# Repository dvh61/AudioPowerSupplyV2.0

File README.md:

# AudioPowerSupplyV2.0
Testing of Kicad/Github capabilities

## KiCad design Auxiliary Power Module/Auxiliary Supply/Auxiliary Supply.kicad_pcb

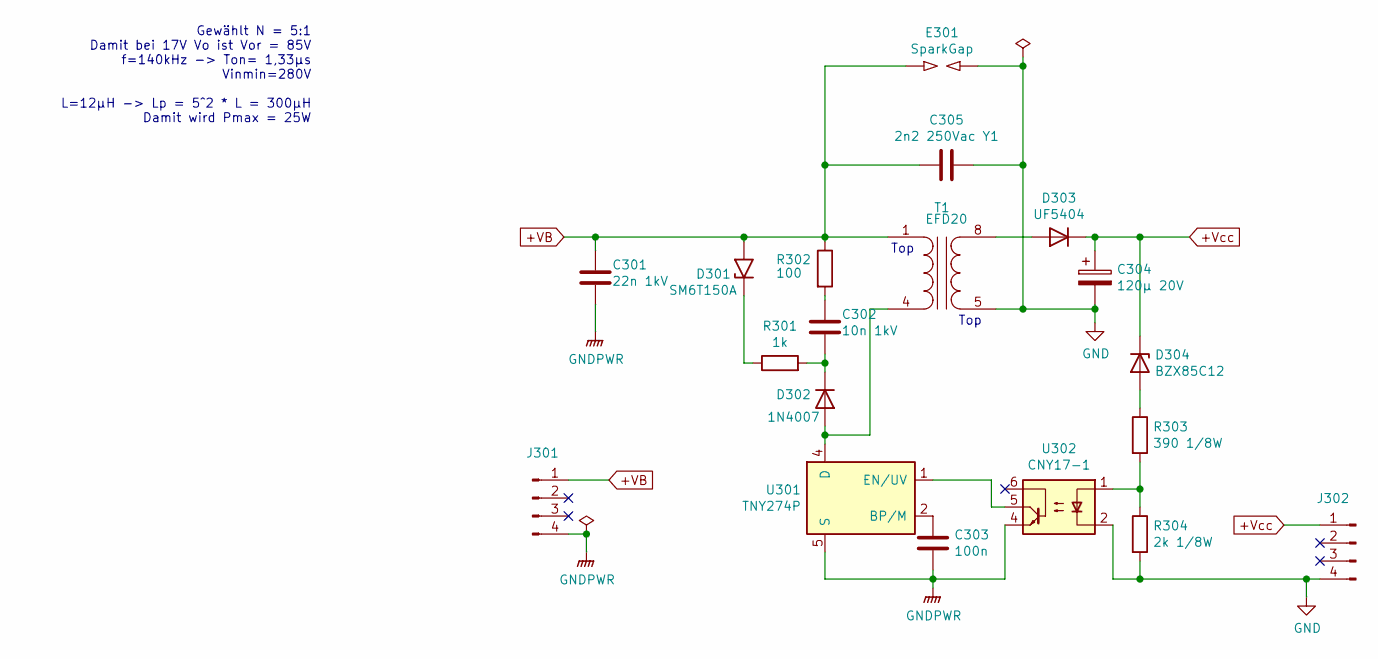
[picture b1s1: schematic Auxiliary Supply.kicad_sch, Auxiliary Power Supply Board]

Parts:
C301: 22n 1kV; C_Disc_D12.5mm_W5.0mm_P7.50mm
C302: 10n 1kV; C_Disc_D12.5mm_W5.0mm_P7.50mm
C303: 100n; C_Rect_L7.2mm_W2.5mm_P5.00mm_FKS2_FKP2_MKS2_MKP2
C304: 120µ 20V; CP_Radial_D6.3mm_P2.50mm
C305: 2n2 250Vac Y1; C_Rect_L18.0mm_W7.0mm_P15.00mm_FKS3_FKP3
D301: SM6T150A; D_SMB_Handsoldering
D302: 1N4007; D_DO-41_SOD81_P2.54mm_Vertical_KathodeUp
D303: UF5404; D_DO-41_SOD81_P2.54mm_Vertical_KathodeUp
D304: BZX85C12; D_DO-41_SOD81_P3.81mm_Vertical_KathodeUp
E301: SparkGap; SparkGap 5000V Top
J301, J302: Conn_01x04_Male; PinHeader_1x04_P2.54mm_Vertical
R301: 1k; R_Axial_DIN0309_L9.0mm_D3.2mm_P5.08mm_Vertical
R302: 100; R_Axial_DIN0309_L9.0mm_D3.2mm_P12.70mm_Horizontal
R303: 390 1/8W; R_Axial_DIN0207_L6.3mm_D2.5mm_P2.54mm_Vertical
R304: 2k 1/8W; R_Axial_DIN0207_L6.3mm_D2.5mm_P2.54mm_Vertical
T1: B66418W1008D1; Mouser Part Number 871-B66418W1008D1
U301: TNY274P; PowerIntegrations_PDIP-8C
U302: CNY17-1; DIP-6_W7.62mm_LongPads

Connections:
+VB: C301.1, C305.1, D301.2 (A2), E301.1, J301.1, R302.1, T1.1 (AA)
+Vcc: C304.1, D303.1 (K), D304.1 (K), J302.1
GND: C304.2, C305.2, E301.2, J302.4, R304.2, T1.5 (SA), U302.2
GNDPWR: C301.2, C303.2, J301.4, U301.5 (S), U301.6 (S), U301.7 (S), U301.8 (S), U302.4
unnamed: C302.1, R302.2
unnamed: C302.2, D302.1 (K), R301.2
unnamed: C303.1, U301.2 (BP/M)
unnamed: D301.1 (A1), R301.1
unnamed: D302.2 (A), T1.4 (AB), U301.4 (D)
unnamed: D303.2 (A), T1.8 (SB)
unnamed: D304.2 (A), R303.1
unnamed: R303.2, R304.1, U302.1
unnamed: U301.1 (EN/UV), U302.5

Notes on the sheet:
Gewählt N = 5:1 Damit bei 17V Vo ist Vor = 85V f=140kHz -> Ton= 1,33µs Vinmin=280V L=12µH -> Lp = 5^2 * L = 300µH Damit wird Pmax = 25W
Top

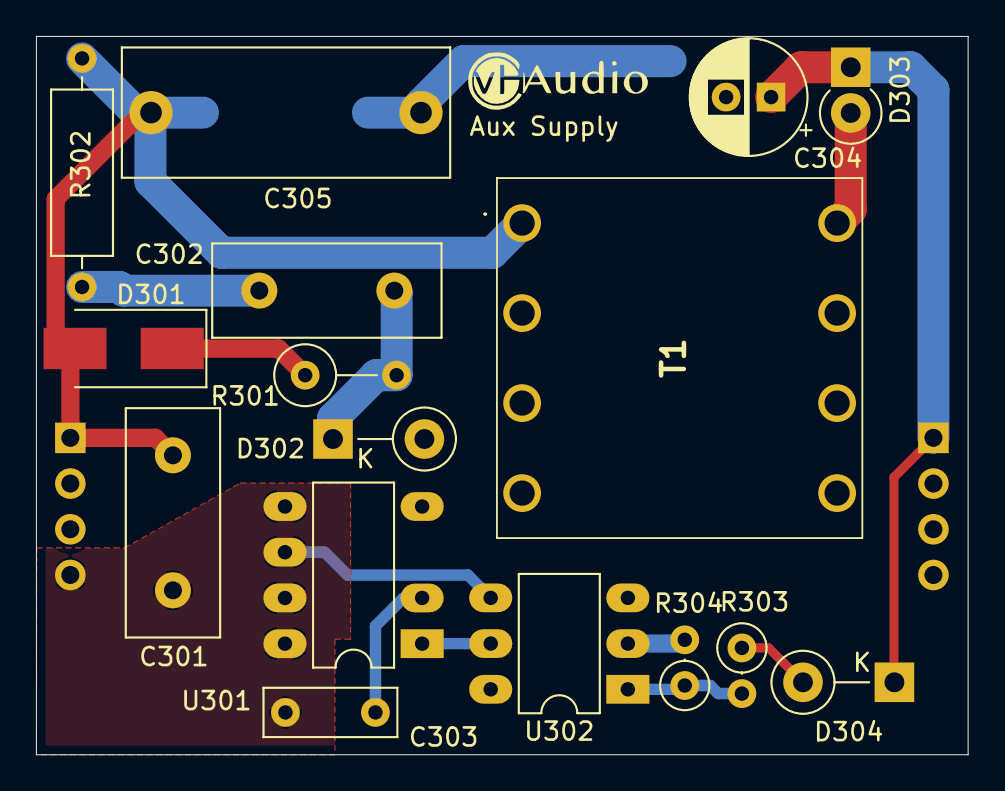
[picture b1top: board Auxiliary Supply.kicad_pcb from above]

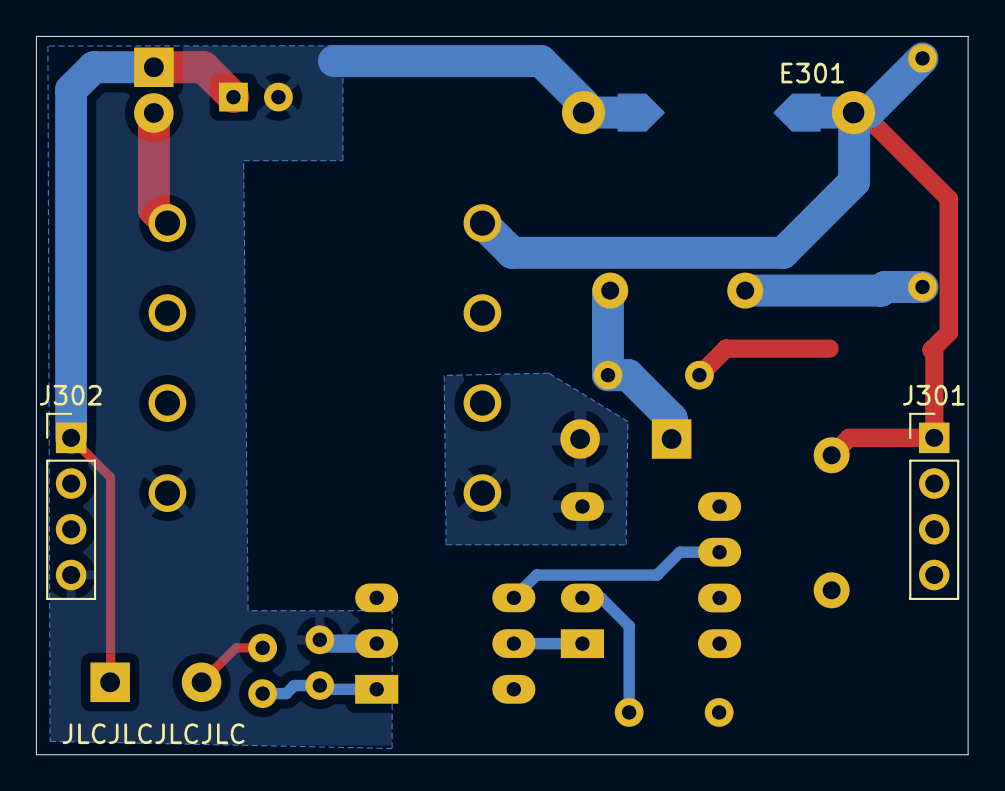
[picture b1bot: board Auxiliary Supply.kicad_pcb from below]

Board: 2 copper layers, 51.8 x 39.9 mm, 19 parts (3 on the bottom side), 13 nets.

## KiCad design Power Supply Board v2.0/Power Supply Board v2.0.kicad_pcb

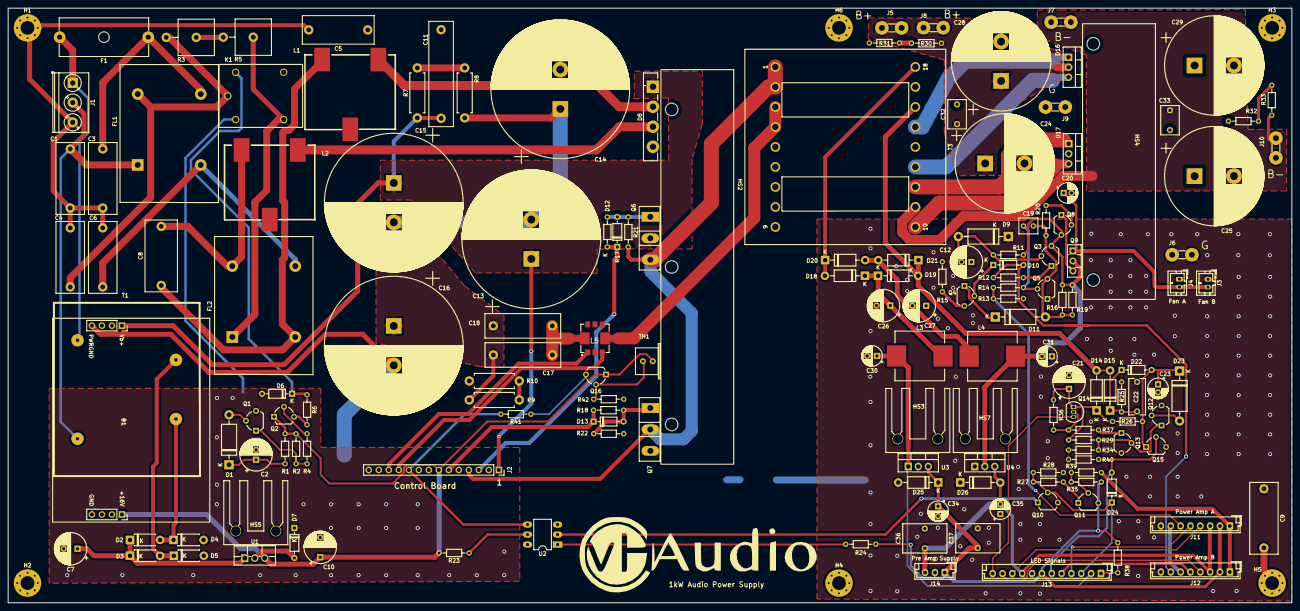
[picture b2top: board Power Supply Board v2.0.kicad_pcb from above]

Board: 2 copper layers, 326.0 x 151.0 mm, 164 parts (1 on the bottom side), 92 nets.

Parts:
B1: AuxPowerSupplyBoard; Aux Power Supply Board
C1, C3, C4, C5, C6, C9: Y2 1n2/500; C_Rect_L18.0mm_W7.0mm_P15.00mm_FKS3_FKP3
C2: 15µ/25; CP_Radial_D8.0mm_P2.50mm
C7, C21, C26, C27: 470µ/35; CP_Radial_D8.0mm_P3.50mm
C8: X2 220n/400; C_Rect_L18.0mm_W8.0mm_P15.00mm_FKS3_FKP3
C10: 47µ/25; CP_Radial_D8.0mm_P5.00mm
C11: 470n/400; C_Rect_L26.5mm_W6.0mm_P22.50mm_MKS4
C12: 1/50; CP_Radial_D8.0mm_P2.50mm
C13, C14, C15, C16: 2200µ/200V; CP_Radial_D35.0mm_P10.00mm_SnapIn
C17, C18: 27n/300V; C_Rect_L19.0mm_W6.0mm_P15.00mm_MKS4
C19: 10n; C_Rect_L4.6mm_W3.8mm_P2.50mm_MKS02_FKP02
C20: 4.7µ/50; CP_Radial_D5.0mm_P2.00mm
C22: 100n; C_Rect_L9.0mm_W4.0mm_P7.50mm_MKT
C23: 33µ/35; CP_Radial_D5.0mm_P2.00mm
C24, C25, C28, C29: 680µ/200V; CP_Radial_D25.0mm_P10.00mm_SnapIn
C30, C31: 47µ/35; CP_Radial_D5.0mm_P2.50mm
C32, C33: 100n/100; C_Rect_L7.2mm_W4.5mm_P5.00mm_FKS2_FKP2_MKS2_MKP2
C34, C35: 10µ/35; CP_Radial_D5.0mm_P2.50mm
C36, C37: 470n; C_Rect_L7.2mm_W11.0mm_P5.00mm_FKS2_FKP2_MKS2_MKP2
D1, D11: 8V2; D_DO-15_P12.70mm_Horizontal
D2, D3, D4, D5: 1N4004; D_DO-41_SOD81_P7.62mm_Horizontal
D6, D7, D10, D12, D13, D22, D24: 1N4148; D_DO-35_SOD27_P7.62mm_Horizontal
D8: GBU2506G; Diode_Bridge_Vishay_GBU
D9, D23: 15V; D_DO-15_P12.70mm_Horizontal
D14, D15, D18, D19, D20, D21: MUR120; D_DO-41_SOD81_P10.16mm_Horizontal
D16, D17: MUR1620CTG; TO-220-3_Vertical
D25, D26: 1N4001; D_DO-41_SOD81_P10.16mm_Horizontal
E1: SparkGap; SparkGap 5000V Top
F1: T6A; Fuseholder_Cylinder-5x20mm_Schurter_0031_8201_Horizontal_Op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
FL1: 7mH/7A; L_CommonMode_Toroid_Vertical_L35mm_W25mm_Px19mm_Py18mm_Keme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
FL2: 7mH//A; L_CommonMode_Toroid_Vertical_L35mm_W25mm_Px19mm_Py18mm_Keme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
H1, H5: MountingHole_Pad; MountingHole_3.5mm_Pad_Via
H2, H3, H4, H6: MountingHole; MountingHole_3.5mm_Pad_Via
HS2: Heatsink; Heatsink_100x45x18mm_3xFixationM3
HS3, HS5, HS7: Heatsink; Heatsink EA2 T220
HS4: Heatsink; Heatsink_70x45x18mm_2xFixationM3
J1: CONN_01X03; TerminalBlock_Phoenix_PT-1,5-3-5.0-H_1x03_P5.00mm_Horizontal
J2: CON_CTRL_Board; PinSocket_1x14_P2.54mm_Vertical
J3, J4: CONN_01X02; JST_PH_B2B-PH-K_1x02_P2.00mm_Vertical
J5, J8: +BH; PCB_Connector_6.35x0.81mm_Vertical
J6, J9: G; PCB_Connector_6.35x0.81mm_Vertical
J7, J10: -BH; PCB_Connector_6.35x0.81mm_Vertical
J11: CON_AMP_A; JST_EH_B8B-EH-A_1x08_P2.50mm_Vertical
J12: CON_AMP_B; JST_EH_B8B-EH-A_1x08_P2.50mm_Vertical
J13: CON_LED; JST_EH_B12B-EH-A_1x12_P2.50mm_Vertical
J14: CONN_01X03; JST_EH_B3B-EH-A_1x03_P2.50mm_Vertical
K1: Pana JS1-12V-F; FINDER_36.11
L1, L2: 57µ/10Arms; L_muRata_6000A
L3, L4: 10µ; L_Wuerth_WE-PD-Typ-LS_Handsoldering
L5: 53100C-I-XFR; 53100C
Q1, Q10, Q11, Q12, Q13, Q15: BC546; TO-92_Wide
Q2, Q4, Q16: MPSA06; TO-92_Wide
Q3, Q5, Q8: MPSA56; TO-92_Wide
Q6, Q7: IRFP460; TO-247-3_Vertical
Q9: MJE350; TO-126-3_Vertical
Q14: MPSA56; TO-92_Inline
R1: 68k; R_Axial_DIN0204_L3.6mm_D1.6mm_P7.62mm_Horizontal
R2: 470; R_Axial_DIN0204_L3.6mm_D1.6mm_P7.62mm_Horizontal
R3, R5: 15/5W; R_Axial_Power_L25.0mm_W9.0mm_P7.62mm_Vertical
R4, R21, R22, R28, R35: 1k; R_Axial_DIN0204_L3.6mm_D1.6mm_P7.62mm_Horizontal
R6: 120; R_Axial_DIN0204_L3.6mm_D1.6mm_P7.62mm_Horizontal
R7, R8, R9, R10: 47k/0.5W; R_Axial_DIN0411_L9.9mm_D3.6mm_P12.70mm_Horizontal
R11: 8k2; R_Axial_DIN0204_L3.6mm_D1.6mm_P7.62mm_Horizontal
R12: 5k6; R_Axial_DIN0204_L3.6mm_D1.6mm_P7.62mm_Horizontal
R13, R14: 330; R_Axial_DIN0204_L3.6mm_D1.6mm_P7.62mm_Horizontal
R15, R20: 220; R_Axial_DIN0204_L3.6mm_D1.6mm_P7.62mm_Horizontal
R16, R23, R41: 12k; R_Axial_DIN0204_L3.6mm_D1.6mm_P7.62mm_Horizontal
R17, R18: 10; R_Axial_DIN0204_L3.6mm_D1.6mm_P7.62mm_Horizontal
R19: 18k; R_Axial_DIN0204_L3.6mm_D1.6mm_P7.62mm_Horizontal
R24: 680; R_Axial_DIN0204_L3.6mm_D1.6mm_P7.62mm_Horizontal
R25: 4k7; R_Axial_DIN0204_L3.6mm_D1.6mm_P7.62mm_Horizontal
R26: 150k; R_Axial_DIN0204_L3.6mm_D1.6mm_P7.62mm_Horizontal
R27, R38, R39: 10k; R_Axial_DIN0204_L3.6mm_D1.6mm_P7.62mm_Horizontal
R29, R36, R37: 220k; R_Axial_DIN0204_L3.6mm_D1.6mm_P7.62mm_Horizontal
R30, R31, R32, R33, R34: 100k; R_Axial_DIN0204_L3.6mm_D1.6mm_P7.62mm_Horizontal
R40: 56k; R_Axial_DIN0204_L3.6mm_D1.6mm_P7.62mm_Horizontal
R42: 120k; R_Axial_DIN0204_L3.6mm_D1.6mm_P7.62mm_Horizontal
T1: Transformer_1P_1S; Transformer_Block_EI42_VC-05VA_1xSec
T3: Half_Bridge_Transformer; ETD44_18Pin_Horizontal_EPCOS-B663661018T
TH1: Thermistor_PTC; PTC Epcos D1052
U1: LM7815ACT; TO-220F-3_Vertical
U2: CNY75G; DIP-6_W7.62mm_LongPads
U3: LM7815ACT; TO-220-3_Vertical
U4: LM7915CT; TO-220-3_Vertical

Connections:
+15V: C34.1, C37.1, D25.1 (K), J11.2, J12.2, J13.7, J14.1, Q11.3 (E), R24.2, R35.2, R38.2, U3.3 (VO)
+16V: B1.5 (+16V), C10.1, J2.7, Q2.1 (E), Q16.1 (E), R1.2, R2.2, R23.2, TH1.1, U1.3 (VO)
+24V: C30.1, J13.2, L3.1, U3.1 (VI)
-15V: C35.2, C36.1, D26.2 (A), J11.3, J12.3, J13.9, J14.3, U4.3 (VO)
-24V: C31.2, L4.1, Q3.3 (C), Q8.3 (C), Q9.2 (C), R11.1, R16.1, R19.1, U4.2 (VI)
/L: F1.2, J1.1, T1.1 (AA)
/N: C1.1, FL1.1, J1.2, T1.2 (AB)
/PR1: J11.6, R13.1, R14.2
/PR2: D10.2 (A), J12.7, R12.2
CLIP_A: J11.5, J13.4
CLIP_B: J12.5, J13.5
CS+: J2.11, L5.3 (SEC2)
CS-: J2.12, L5.1 (SEC1)
Earth_Protective: C1.2, C3.2, C4.2, C5.2, C6.2, H1.1, J1.3
FAULT: D24.1 (K), J13.3, Q10.2 (B), R27.1, R28.2
GND: C9.1, C12.1, C20.2, C21.2, C22.2, C23.2, C24.2, C25.1, C26.2, C27.1, C28.2, C29.1, C30.2, C31.1, C32.2, C33.1, C34.2, C35.1, C36.2, C37.2, D9.1 (K), D17.2 (common), D25.2 (A), D26.1 (K), E1.2, J3.1, J4.1, J6.1, J9.1, J11.8, J12.8, J13.8, J14.2, Q5.1 (E), Q10.3 (E), Q12.3 (E), Q13.3 (E), Q15.3 (E), R13.2, R15.2, R25.2, R28.1, R31.2, R32.1, R34.2, R40.2, T3.14, T3.17, U3.2 (GND), U4.1 (GND)
GNDA: B1.4 (PWRGND), B1.8 (GND), C2.2, C5.1, C7.2, C10.2, C11.1, C14.2, C16.2, D4.2 (A), D5.2 (A), D6.2 (A), D7.1 (K), D8.4 (-), E1.1, J2.14, K1.A1, Q1.3 (E), Q7.3 (S), R10.2, R22.2, R42.2
HO: D12.1 (K), J2.3, R17.2
LO: D13.1 (K), J2.6, R18.2
MUTE: J13.12, Q14.3 (C)
unnamed: C2.1, D1.1 (K), R1.1
unnamed: C3.1, F1.1, FL1.3
unnamed: C4.1, FL1.4, K1.11, R3.2
unnamed: C6.1, FL1.2, FL2.3
unnamed: C7.1, D2.1 (K), D3.1 (K), U1.1 (VI)
unnamed: C8.1, FL2.2, L1.2
unnamed: C8.2, FL2.4, L2.2
unnamed: C9.2, H5.1
unnamed: C12.2, D9.2 (A), Q3.2 (B), R11.2
unnamed: C13.2, C14.1, C15.2, C16.1, C17.2, C18.1, R8.2, R9.1
unnamed: C17.1, C18.2, L5.8 (PRI2)
unnamed: C19.1, Q5.2 (B), R14.1
unnamed: C19.2, D11.2 (A), Q5.3 (C), R16.2, R19.2, R20.2
unnamed: C20.1, J3.2, J4.2, Q9.1 (E)
unnamed: C21.1, D14.1 (K), Q14.1 (E), R26.1, R29.1, R36.1
unnamed: C22.1, D15.1 (K), D22.1 (K), R25.1
unnamed: C23.1, D22.2 (A), D23.1 (K), Q15.1 (C), R26.2
unnamed: C24.1, C28.1, C32.1, D16.2 (common), J5.1, J8.1, R30.1
unnamed: C25.2, C29.2, C33.2, J7.1, J10.1, R33.2, T3.11
unnamed: C26.1, D18.1 (K), D19.1 (K), L3.2
unnamed: C27.2, D20.2 (A), D21.2 (A), L4.2
unnamed: D1.2 (A), Q1.2 (B)
unnamed: D2.2 (A), D4.1 (K), T1.4 (SB)
unnamed: D3.2 (A), D5.1 (K), T1.3 (SA)
unnamed: D6.1 (K), K1.A2, R6.1
unnamed: D7.2 (A), U1.2 (GND)
unnamed: D8.2 (~~), L1.1
unnamed: D8.3 (~~), L2.1
unnamed: D10.1 (K), Q4.2 (B)
unnamed: D11.1 (K), Q4.1 (E)
unnamed: D12.2 (A), Q6.1 (G), R17.1, R21.1
unnamed: D13.2 (A), Q7.1 (G), R18.1, R22.1
unnamed: D14.2 (A), D15.2 (A), D19.2 (A), D21.1 (K), T3.16
unnamed: D16.1 (A1), T3.15
unnamed: D16.3 (A2), T3.13
unnamed: D18.2 (A), D20.1 (K), T3.18
unnamed: D23.2 (A), Q12.2 (B)
unnamed: FL2.1, K1.14, R5.1
unnamed: J11.1, J12.1, R39.1
unnamed: J11.7, J12.6
unnamed: L5.7 (PRI1), T3.3, T3.4
unnamed: Q1.1 (C), R2.1, R4.2
unnamed: Q2.2 (B), R4.1
unnamed: Q2.3 (C), R6.2
unnamed: Q3.1 (E), R12.1
unnamed: Q4.3 (C), R15.1
unnamed: Q8.1 (E), Q9.3 (B)
unnamed: Q8.2 (B), R20.1
unnamed: Q10.1 (C), U2.2
unnamed: Q11.1 (C), R27.2
unnamed: Q11.2 (B), R35.1, R39.2
unnamed: Q12.1 (C), Q13.2 (B), R29.2, R34.1
unnamed: Q13.1 (C), R37.2
unnamed: Q14.2 (B), R36.2, R37.1
unnamed: Q16.2 (B), R42.1, TH1.2
unnamed: Q16.3 (C), R41.1
unnamed: R3.1, R5.2
unnamed: R7.2, R8.1
unnamed: R9.2, R10.1
unnamed: R23.1, U2.5
unnamed: R24.1, U2.1
unnamed: R30.2, R31.1
unnamed: R32.2, R33.1
unnamed: D17.3 (A2), T3.10
unnamed: D17.1 (A1), T3.12
PWR: J13.1, R38.1
SIG_A: J11.4, J13.10
SIG_B: J12.4, J13.11
Shutdown: J2.10, R41.2, U2.4
TEMP: D24.2 (A), J13.6, Q15.2 (B), R40.1
VB: B1.1 (+Vb), C11.2, C13.1, C15.1, D8.1 (+), J2.1, Q6.2 (D), R7.1
VS: J2.4, Q6.3 (S), Q7.2 (D), R21.2, T3.1, T3.2

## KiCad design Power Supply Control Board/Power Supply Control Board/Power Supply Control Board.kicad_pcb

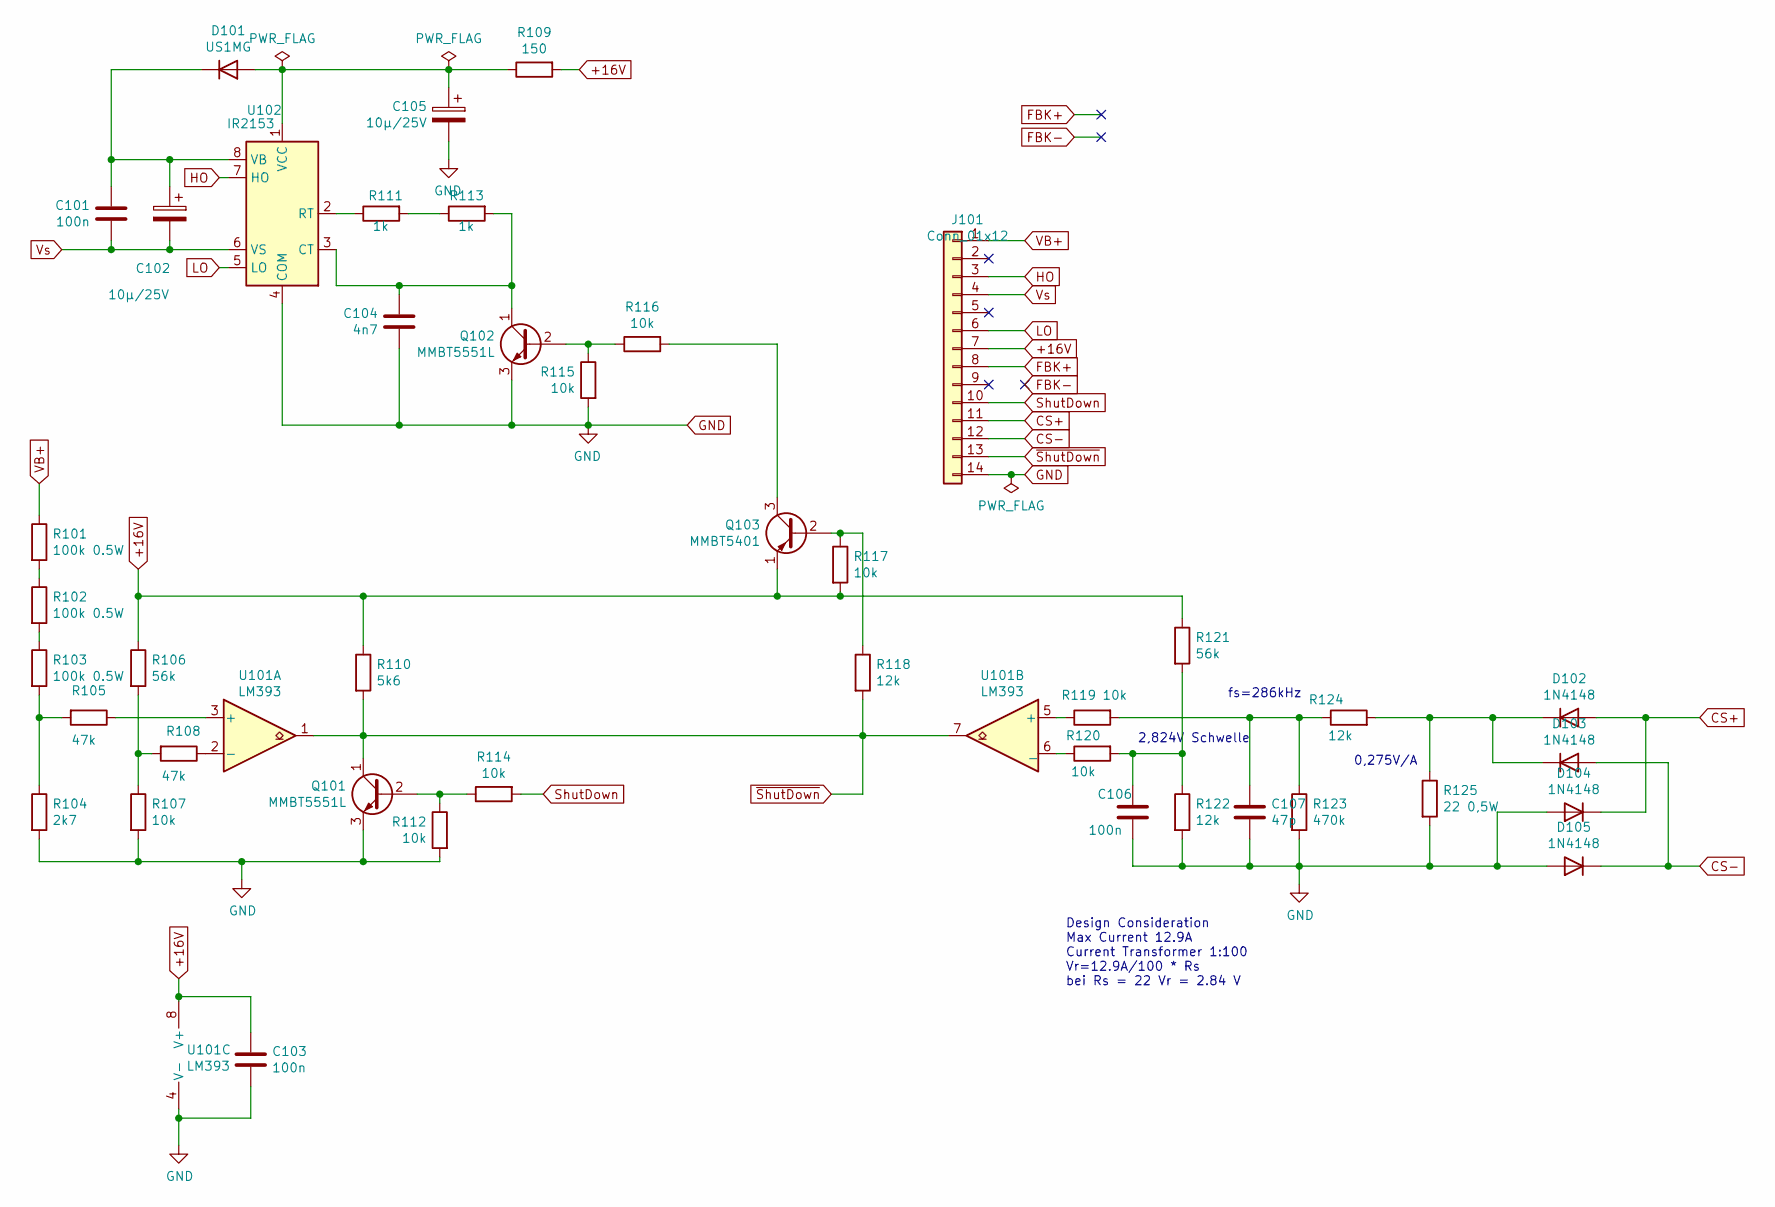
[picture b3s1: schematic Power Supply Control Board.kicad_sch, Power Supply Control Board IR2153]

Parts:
C101, C103, C106: 100n; C_0805_2012Metric
C102, C105: 10µ/25V; C_0805_2012Metric
C104: 4n7; C_0805_2012Metric
C107: 47p; C_0402_1005Metric
D101: US1MG; D_SMA
D102, D103, D104, D105: 1N4148; D_SOD-123
J101: Conn_01x12; PinHeader_1x14_P2.54mm_Horizontal
Q101, Q102: MMBT5551L; SOT-23
Q103: MMBT5401; SOT-23
R101, R102, R103: 100k 0.5W; R_1206_3216Metric
R104: 2k7; R_0805_2012Metric
R105, R108: 47k; R_0805_2012Metric
R106, R121: 56k; R_0805_2012Metric
R107, R112, R114, R115, R116, R117, R119, R120: 10k; R_0805_2012Metric
R109: 150; R_0805_2012Metric
R110: 5k6; R_0805_2012Metric
R111, R113: 1k; R_0805_2012Metric
R118, R122, R124: 12k; R_0805_2012Metric
R123: 470k; R_0805_2012Metric
R125: 22 0,5W; R_1206_3216Metric
U101: LM393; SOIC-8_3.9x4.9mm_P1.27mm
U102: IR2153; SOIC-8_3.9x4.9mm_P1.27mm; LCSC C79666

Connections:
+16V: C103.1, J101.7, Q103.1 (E), R106.1, R109.2, R110.1, R117.2, R121.1, U101.8 (V+)
CS+: D102.2 (A), D104.1 (K), J101.11
CS-: D103.2 (A), D105.1 (K), J101.12
FBK+: J101.8
GND: C103.2, C104.2, C105.2, C106.2, C107.2, D104.2 (A), D105.2 (A), J101.14, Q101.3 (E), Q102.3 (E), R104.2, R107.2, R112.2, R115.2, R122.2, R123.2, R125.2, U101.4 (V-), U102.4 (COM)
HO: J101.3, U102.7 (HO)
LO: J101.6, U102.5 (LO)
unnamed: C101.1, C102.1, D101.1 (K), U102.8 (VB)
unnamed: C104.1, Q102.1 (C), R113.2, U102.3 (CT)
unnamed: C106.1, R120.2, R121.2, R122.1
unnamed: C107.1, R119.2, R123.1, R124.1
unnamed: C105.1, D101.2 (A), R109.1, U102.1 (VCC)
unnamed: D102.1 (K), D103.1 (K), R124.2, R125.1
unnamed: Q101.2 (B), R112.1, R114.1
unnamed: Q102.2 (B), R115.1, R116.1
unnamed: Q103.2 (B), R117.1, R118.1
unnamed: Q103.3 (C), R116.2
unnamed: R101.2, R102.1
unnamed: R102.2, R103.1
unnamed: R103.2, R104.1, R105.2
unnamed: R105.1, U101.3 (+)
unnamed: R106.2, R107.1, R108.2
unnamed: R108.1, U101.2 (-)
unnamed: R111.1, U102.2 (RT)
unnamed: R111.2, R113.1
unnamed: R119.1, U101.5 (+)
unnamed: R120.1, U101.6 (_)
ShutDown: J101.10, R114.2
VB+: J101.1, R101.1
Vs: C101.2, C102.2, J101.4, U102.6 (VS)
~ShutDown: J101.13, Q101.1 (C), R110.2, R118.2, U101.1, U101.7

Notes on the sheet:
Design Consideration Max Current 12.9A Current Transformer 1:100 Vr=12.9A/100 * Rs bei Rs = 22 Vr = 2.84 V
2,824V Schwelle
fs=286kHz
0,275V/A

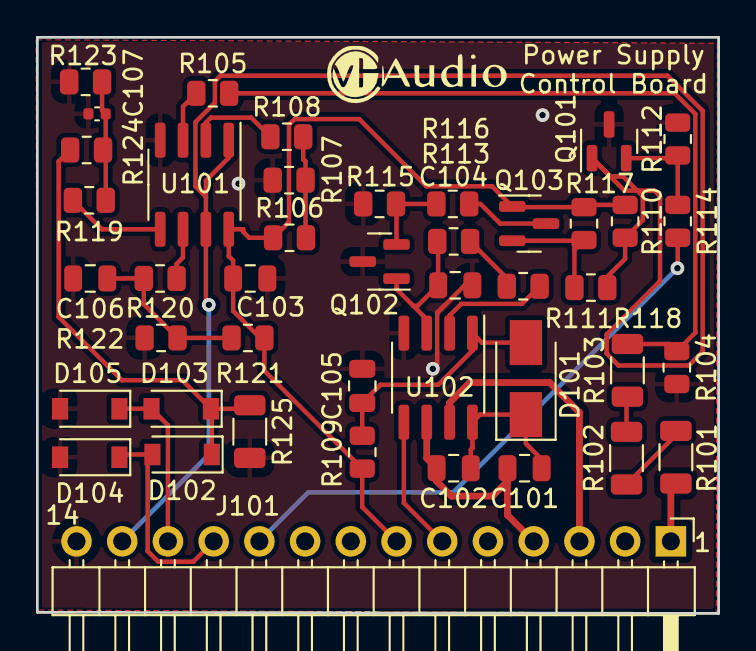
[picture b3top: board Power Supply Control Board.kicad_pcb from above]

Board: 2 copper layers, 37.8 x 32.0 mm, 43 parts (0 on the bottom side), 30 nets.

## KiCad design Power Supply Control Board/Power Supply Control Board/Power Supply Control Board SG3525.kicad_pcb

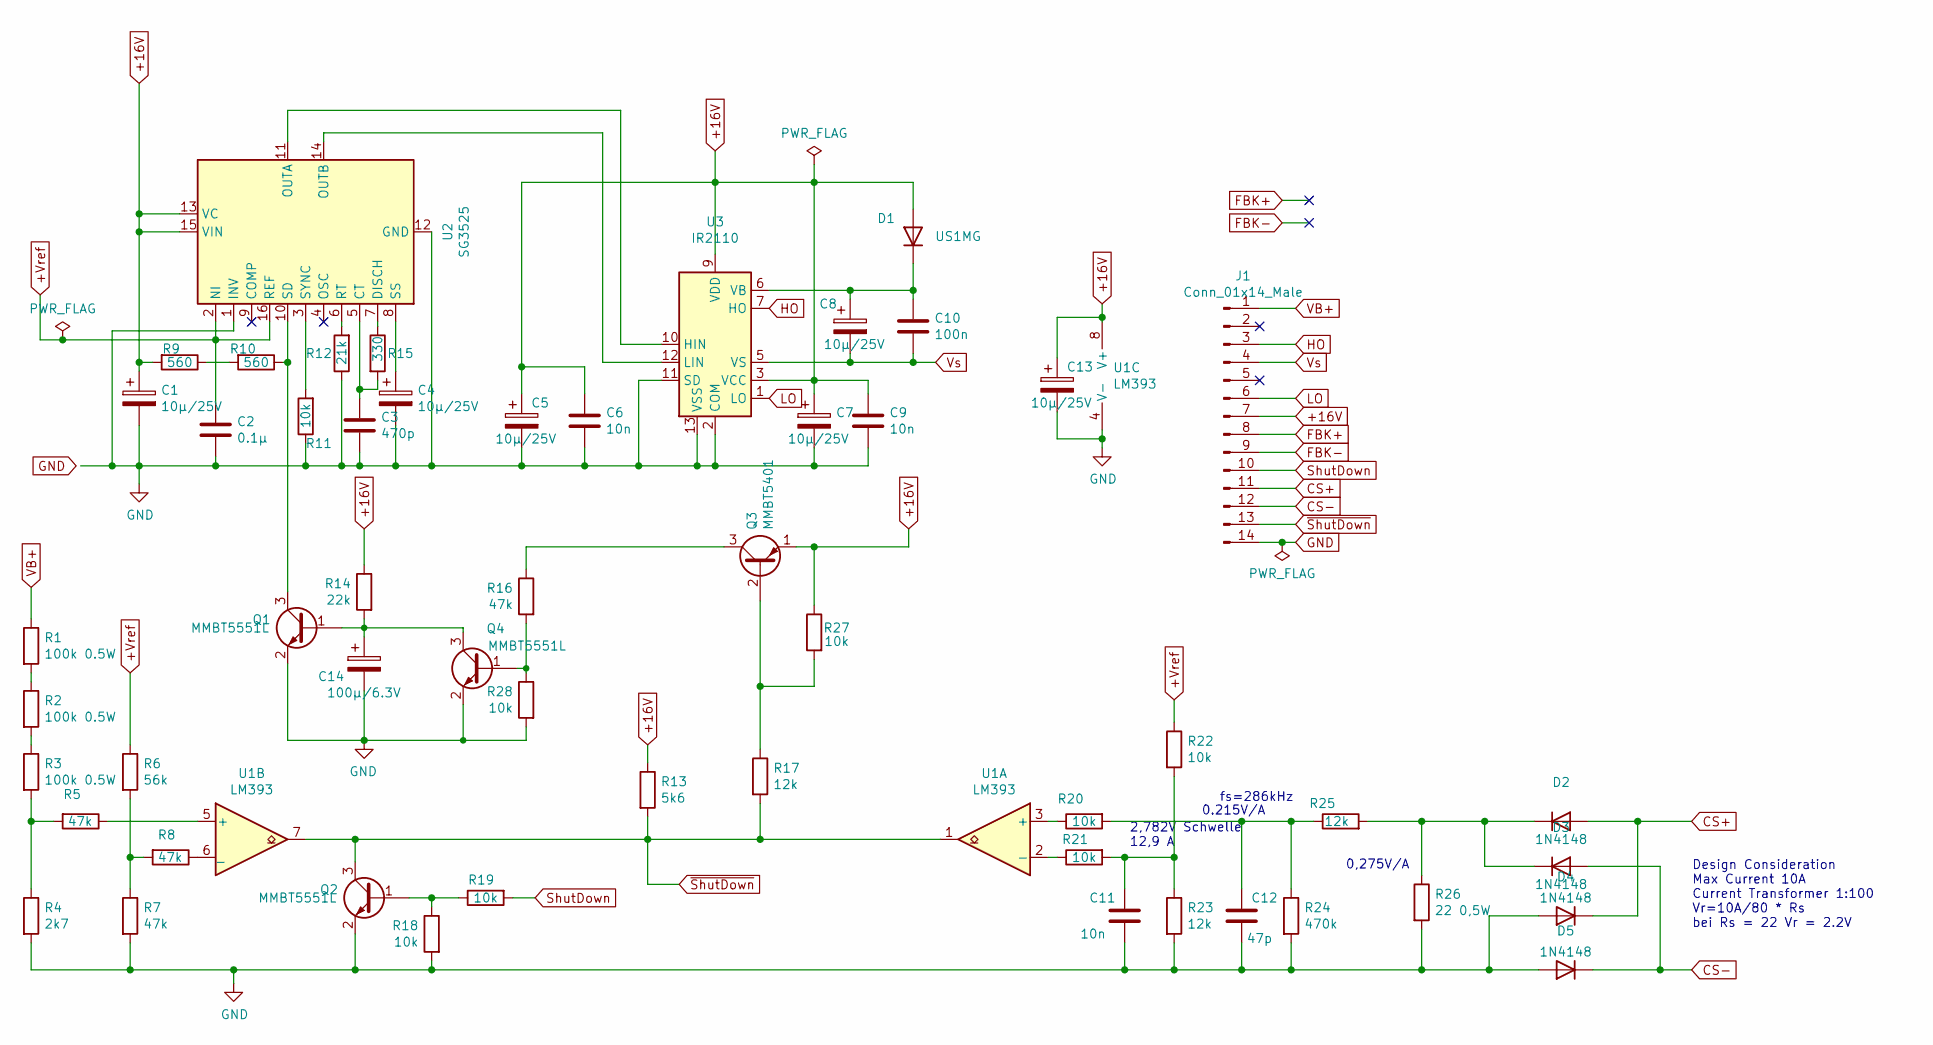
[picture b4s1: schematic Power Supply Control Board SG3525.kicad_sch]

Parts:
C1, C4, C5, C7, C8, C13: 10µ/25V; C_0805_2012Metric; LCSC C15850
C2: 0.1µ; C_0805_2012Metric; LCSC C49678
C3: 470p; C_0402_1005Metric; LCSC C1537
C6: 10n; C_0402_1005Metric; LCSC C15195
C9, C11: 10n; C_0402_1005Metric
C10: 100n; C_0805_2012Metric; LCSC C49678
C12: 47p; C_0402_1005Metric; LCSC C1567
C14: 100µ/6.3V; CP_EIA-3528-21_Kemet-B; LCSC C134723
D1: US1MG; D_SMA; LCSC C412437
D2, D3, D4, D5: 1N4148; D_SOD-123; LCSC C81598
J1: Conn_01x14_Male; PinHeader_1x14_P2.54mm_Horizontal
Q1, Q2, Q4: MMBT5551L; SOT-23
Q3: MMBT5401; SOT-23
R1, R2, R3: 100k 0.5W; R_1206_3216Metric
R4: 2k7; R_0805_2012Metric
R5, R7, R8, R16: 47k; R_0805_2012Metric
R6: 56k; R_0805_2012Metric
R9, R10: 560; R_0805_2012Metric
R11, R18, R19, R20, R21, R22, R27, R28: 10k; R_0805_2012Metric
R12: 21k; R_0805_2012Metric
R13: 5k6; R_0805_2012Metric
R14: 22k; R_0805_2012Metric
R15: 330; R_0805_2012Metric
R17, R23, R25: 12k; R_0805_2012Metric
R24: 470k; R_0805_2012Metric
R26: 22 0,5W; R_1206_3216Metric
U1: LM393; SOIC-8_3.9x4.9mm_P1.27mm
U2: SG3525; SO-16_3.9x9.9mm_P1.27mm; LCSC C68323
U3: IR2110; SOIC-16W_7.5x10.3mm_P1.27mm; LCSC C2968

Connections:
+16V: C1.1, C5.1, C6.1, C7.1, C9.1, C13.1, D1.2 (A), J1.7, Q3.1 (E), R9.2, R13.1, R14.1, R27.1, U1.8 (V+), U2.13 (VC), U2.15 (VIN), U3.3 (VCC), U3.9 (VDD)
+Vref: C2.1, R6.1, R22.1, U2.2 (NI), U2.16 (REF)
CS+: D2.2 (A), D4.1 (K), J1.11
CS-: D3.2 (A), D5.1 (K), J1.12
FBK+: J1.8
FBK-: J1.9
GND: C1.2, C2.2, C3.2, C4.2, C5.2, C6.2, C7.2, C9.2, C11.2, C12.2, C13.2, C14.2, D4.2 (A), D5.2 (A), J1.14, Q1.2 (E), Q2.2 (E), Q4.2 (E), R4.2, R7.2, R11.1, R12.1, R18.2, R23.2, R24.2, R26.2, R28.2, U1.4 (V-), U2.1 (INV), U2.12 (GND), U3.2 (COM), U3.11 (SD), U3.13 (VSS)
HO: J1.3, U3.7 (HO)
LO: J1.6, U3.1 (LO)
unnamed: C3.1, R15.2, U2.5 (CT)
unnamed: C4.1, U2.8 (SS)
unnamed: C8.1, C10.1, D1.1 (K), U3.6 (VB)
unnamed: C11.1, R21.2, R22.2, R23.1
unnamed: C12.1, R20.2, R24.1, R25.1
unnamed: C14.1, Q1.1 (B), Q4.3 (C), R14.2
unnamed: D2.1 (K), D3.1 (K), R25.2, R26.1
unnamed: Q1.3 (C), R10.1, U2.10 (SD)
unnamed: Q2.1 (B), R18.1, R19.1
unnamed: Q3.2 (B), R17.1, R27.2
unnamed: Q3.3 (C), R16.1
unnamed: Q4.1 (B), R16.2, R28.1
unnamed: R1.2, R2.1
unnamed: R2.2, R3.1
unnamed: R3.2, R4.1, R5.2
unnamed: R5.1, U1.5 (+)
unnamed: R6.2, R7.1, R8.2
unnamed: R8.1, U1.6 (_)
unnamed: R9.1, R10.2
unnamed: R11.2, U2.3 (SYNC)
unnamed: R12.2, U2.6 (RT)
unnamed: R15.1, U2.7 (DISCH)
unnamed: R20.1, U1.3 (+)
unnamed: R21.1, U1.2 (-)
unnamed: U2.11 (OUTA), U3.10 (HIN)
unnamed: U2.14 (OUTB), U3.12 (LIN)
ShutDown: J1.10, R19.2
VB+: J1.1, R1.1
Vs: C8.2, C10.2, J1.4, U3.5 (VS)
~ShutDown: J1.13, Q2.3 (C), R13.2, R17.2, U1.1, U1.7

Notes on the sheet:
2,782V Schwelle 12,9 A
0.215V/A
fs=286kHz
0,275V/A
Design Consideration Max Current 10A Current Transformer 1:100 Vr=10A/80 * Rs bei Rs = 22 Vr = 2.2V

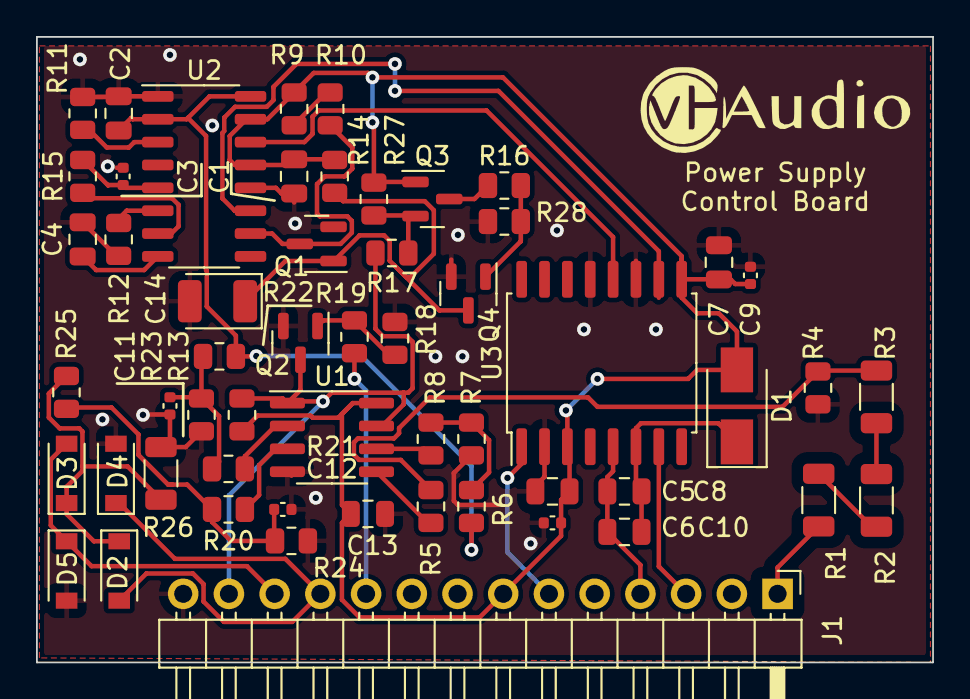
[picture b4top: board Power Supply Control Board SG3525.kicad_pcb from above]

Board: 2 copper layers, 49.8 x 34.8 mm, 55 parts (0 on the bottom side), 37 nets.

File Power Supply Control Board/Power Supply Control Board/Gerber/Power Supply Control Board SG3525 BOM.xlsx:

Comment | Designator | Footprint | LCSC Part Number
10uF | C1,C4,C5,C7,C8,C13 | 0805 | C15850
100n | C10 | 0805 | C49678
47p | C12 | 0402 | C1567
100uF | C14 | CASE-B_3528 | C16133
0.1uF | C2 | 0805 | C49678
470p | C3 | 0402 | C1537
10n | C6,C9,C11 | 0402 | C15195
US1MG | D1 | SMA | C412437
1N4148 | D2,D3,D4,D5 | SOD-123 | C81598
MMBT5551L | Q1,Q2,Q4 | SOT-23 | C2145
MMBT5401 | Q3 | SOT-23 | C8326
100k | R1,R2,R3 | 1206 | C17900
10k | R11,R18,R19,R20,R21,R22,R27,R28 | 0805 | C17414
22k | R12 | 0805 | C17560
5k6 | R13 | 0805 | C4382
22k | R14 | 0805 | C17560
330 | R15 | 0805 | C17630
470k | R24 | 0805 | C17709
22 | R26 | 1206 | C17958
2k7 | R4 | 0805 | C17530
12k | R17,R23,R25 | 0805 | C17444
47k | R5,R7,R8,R16 | 0805 | C17713
56k | R6 | 0805 | C17756
560 | R9,R10 | 0805 | C28636
LM393 | U1 | SOIC-8_3.9x4.9x1.27P | C7955
SG3525 | U2 | SOIC-16_3.9x9.9x1.27P | C68323
IR2110 | U3 | SOIC-16_7.5x10.3x1.27P | C2968

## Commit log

2021-03-29 Start of with basic Version
2021-03-29 Version with SMPS Aux Power
2021-03-29 Version with transformer Aux
2021-03-30 Change to a modular drawing and design
2021-03-31 Add protection circuits
2021-04-09 Finish design of SG3525 Board into SMD
2021-04-09 Add Top Layer Zones and some graphics to Main Board V2.0
2021-04-14 Add stitching and move some components around, so taht they no longer are top of each other
2021-04-23 Cleanup of current status for V3.0
